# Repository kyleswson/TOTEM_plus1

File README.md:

<picture align="center">
  <source media="(prefers-color-scheme: dark)" srcset="/docs/images/TOTEM_logo_dark.svg">
  <source media="(prefers-color-scheme: light)" srcset="/docs/images/TOTEM_logo_bright.svg">
  
</picture>

<h1 align="center">T O T E M</h1>

TOTEM is a 38 key column-staggered choc split keyboard. It is meant to be used with a [Seeed Studio XIAO nRF52840 BLE](https://www.seeedstudio.com/Seeed-XIAO-BLE-nRF52840-p-5201.html) or [XIAO RP2040](https://www.seeedstudio.com/XIAO-RP2040-v1-0-p-5026.html).
It was created for the SEEED XIAO keyboard contest.\
[Here](https://www.hackster.io/geist/totem-a-tiny-splitkeyboard-with-splay-cb2e43) you can read about the process of making it.

## Companion Totem (TOTEM+1)
Totem+1 is a modified version of TOTEM by GEIGEIGEIST. It has additional one key on inner index column of each side (total 40 keys). This is because typing in Korean needs the "B" key on the right hand side. So I added additional B key on the right. And to make this keyboard symmetrical, I added it on the left side too. 

The inner thumb keys have been replaced to [EVQWGD001 roller encoders](https://a.aliexpress.com/_c3mfh3fF). Thought this will be handy for navigating cursor while typing. These are very expensive now(25$ for 1) but luckily I got it for 5$ each few years ago. \
I also found some alternatives that you can consider. But you may need to edit the PCB since the footprint will be different.\
https://github.com/kumamuk-git/CKW12 \
https://github.com/Taro-Hayashi/THQWGD001 \
https://github.com/EverydayErgo/MEH01 

For the batteries, I used this [305060 1100mAh battery](https://a.aliexpress.com/_c3kIPq6d) since I wanted long battery life. 

***

## LAYOUT

***

## PCB

[Here](/PCB/) you can find the KiCad files and Gerbers for the TOTEM.

***

## CASE

You can use the TOTEM without a case, but [here](/case/) you can find one I made for it.

***

## BUILD GUIDE

The build guide for the TOTEM can be found [here](/docs/buildguide.md).

***

## FIRMWARE

[QMK (VIAL) precompiled](/firmware/QMK/) or [QMK (VIAL) source](/firmware/QMK/VIAL_source/) for the TOTEM (wired using the XIAO RP2040)\
[ZMK precompiled](/firmware/ZMK/) or [ZMK source (outdated)](https://github.com/GEIGEIGEIST/zmk-config-totem) for the TOTEM (wireless using the XIAO BLE)

***

## BUY

You can buy TOTEM kits and finished builds on [keeb.supply](https://keeb.supply/products/geist-totem) (based in Germany)

***

## PHOTOS

This is the TOTEM in a black resin case

\
\

This is the TOTEM with a black resin tenting bottom plate

\
[Video by *Wolfgang's Channel* showing the tenting system in action](https://youtu.be/rvM2BthjEI4?si=mTJVdPeZstshnDyo)

***

## CREDITS

### INSPIRATION

I've added the additional pinky key to make the TOTEM compatible with the layout boards like the [Balbuzard](https://github.com/brow/balbuzard) by [Tom Brow](https://github.com/brow) and the [Osprette](https://github.com/smores56/osprette) by [Sam Mohr](https://github.com/smores56) use, where you put the keybinding of the top left and right keys on an outer pinky key.

### HELP FIXING THINGS

People who helped me create this board and fix stuff

#### PCB
- [Marco "Bob"](https://github.com/GroooveBob)

#### CASE
- [Freya](https://github.com/freya-irl)
- [Bubbleology](https://github.com/bubbleology)

#### FIRMWARE
- [Cem Aksoylar](https://github.com/caksoylar)
- [Grinnie](https://github.com/regicidalplutophage)
- [Alaa Saad Mansour](https://github.com/AlaaSaadAbdo)
- [pekudzu](https://github.com/pekudzu)

If you build a TOTEM I would be pretty happy to see some pictures. And if you want to leave me a tip you can do this [here](https://ko-fi.com/geigeigeist) (but please don't feel pressured)

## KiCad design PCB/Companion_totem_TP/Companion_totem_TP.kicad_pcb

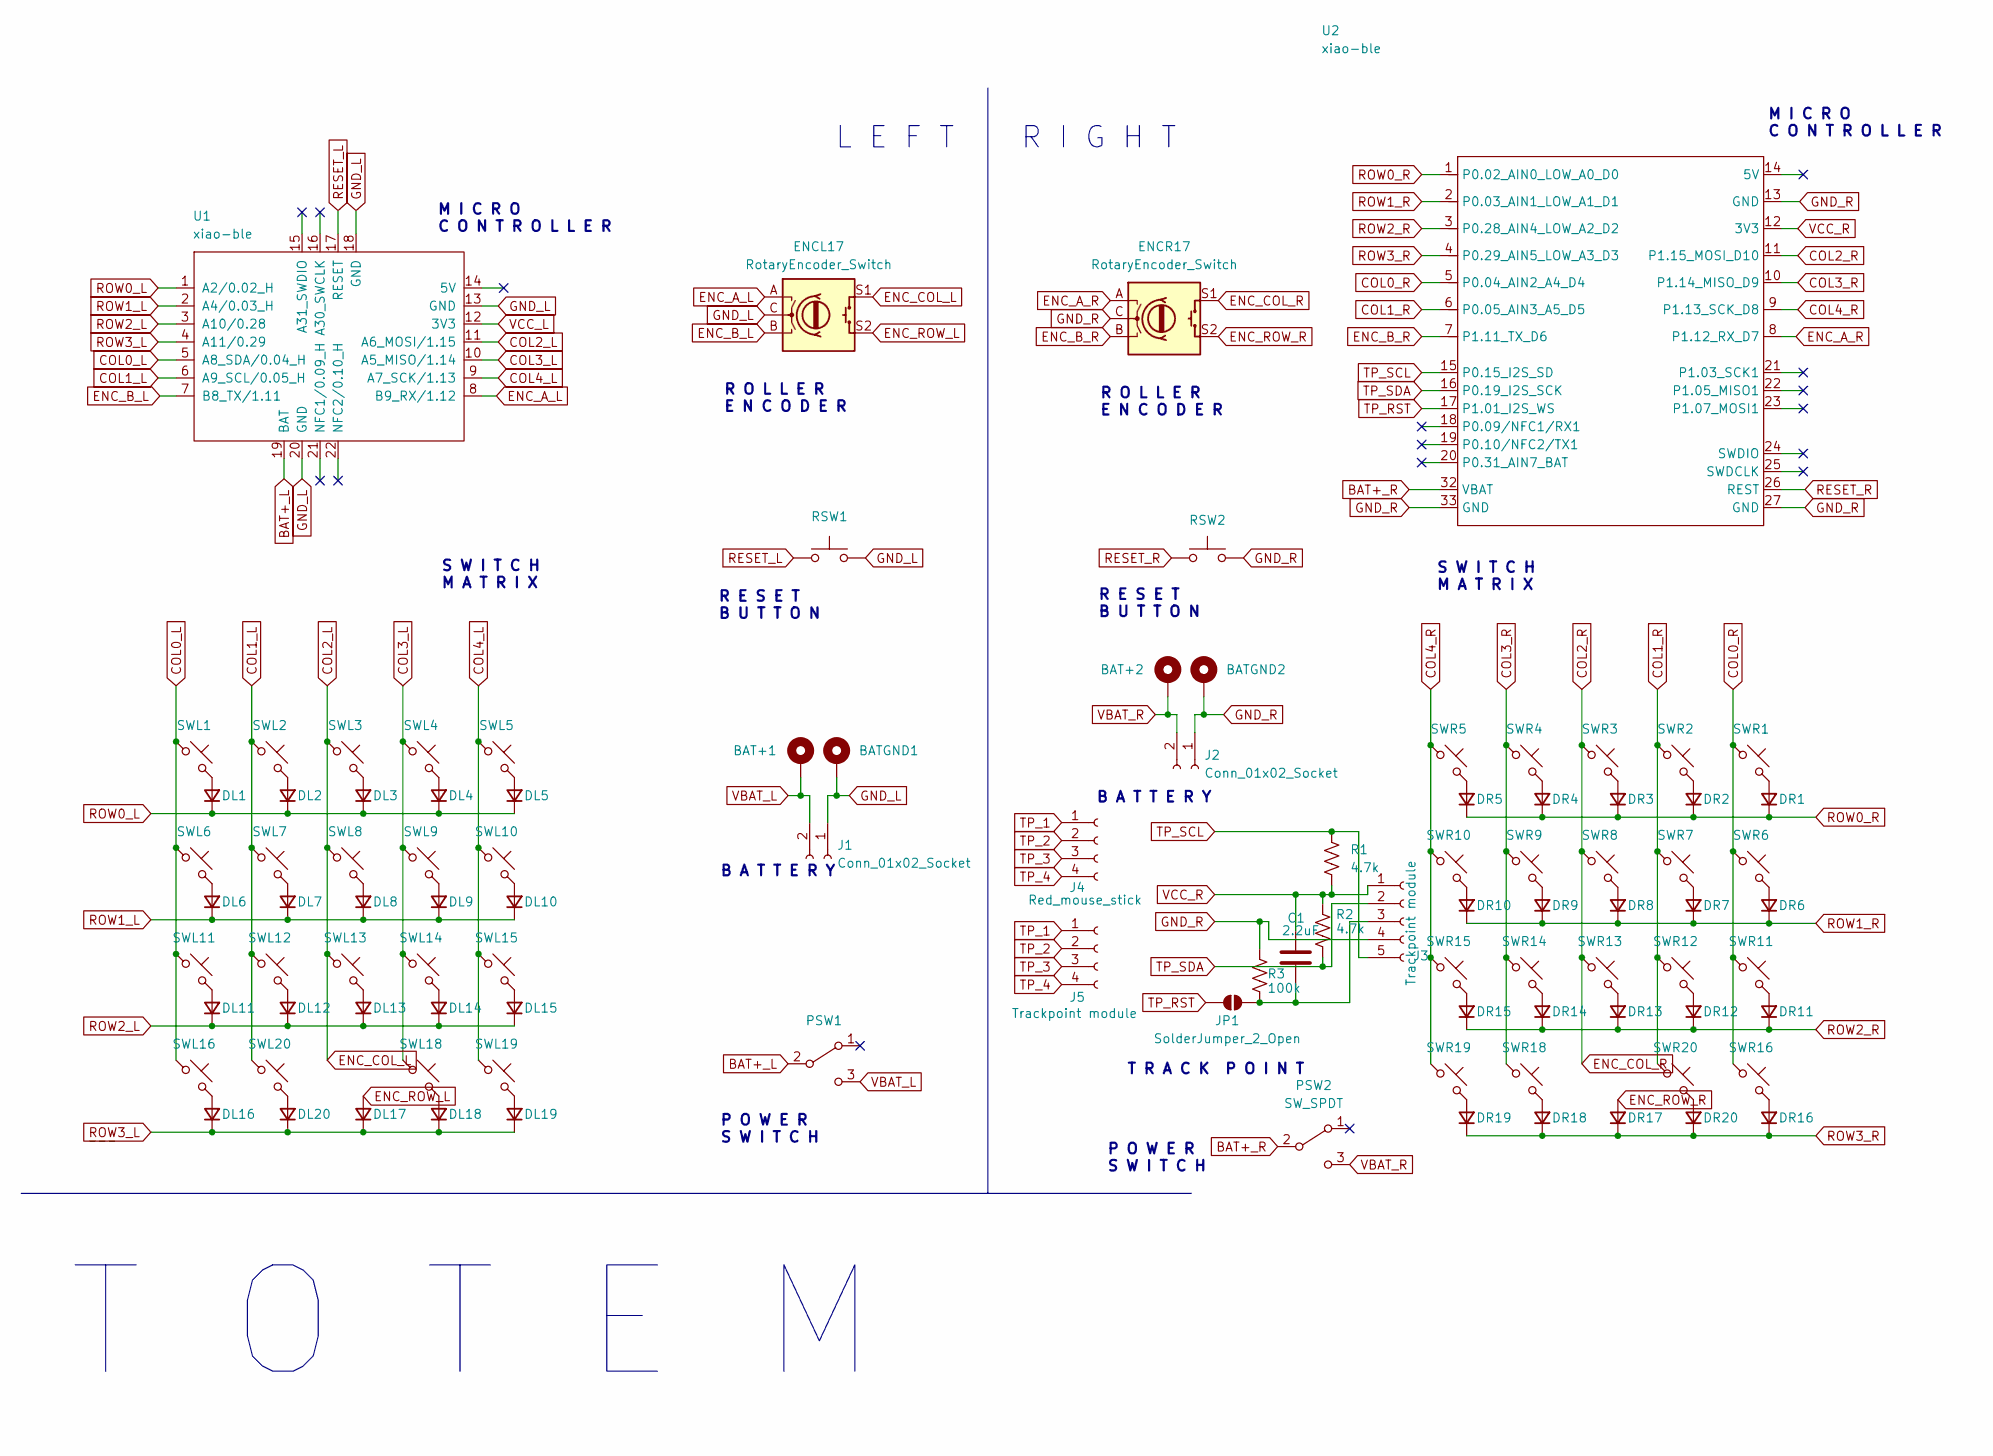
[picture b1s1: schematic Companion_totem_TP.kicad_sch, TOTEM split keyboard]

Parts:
BAT+1, BAT+2: +; BatteryPad
BATGND1, BATGND2: -; BatteryPad
C1: 2.2uF; C_0603_1608Metric_Pad1.08x0.95mm_HandSolder
DL1, DL2, DL3, DL4, DL5, DL6, DL7, DL8, DL9, DL10, DL11, DL12, DL13, DL14, DL15, DL16, DL17, DL18, DL19, DL20: D_Small; Diode_SOD123
DR1, DR2, DR3, DR4, DR5, DR6, DR7, DR8, DR9, DR10, DR11, DR12, DR13, DR14, DR15, DR16, DR17, DR18, DR19, DR20: D_Small; Diode_SOD123
ENCL17: RotaryEncoder_Switch; RollerEncoder+SW_horizontal
ENCR17: RotaryEncoder_Switch; RollerEncoder_SW_Vertical
J1, J2: Conn_01x02_Socket
J3: Trackpoint module; PinSocket_1x05_P2.54mm_Vertical
J4: Red_mouse_stick; T460S_TP
J5: Trackpoint module; TP_input
JP1: SolderJumper_2_Open; Jumper
PSW1, PSW2: SW_SPDT; MSK12C02
R1, R2: 4.7k; R_0603_1608Metric_Pad0.98x0.95mm_HandSolder
R3: 100k; R_0603_1608Metric_Pad0.98x0.95mm_HandSolder
RSW1, RSW2: SW_Push; SKHLLCA010
SWL1, SWL2, SWL3, SWL4, SWL5, SWL6, SWL7, SWL8, SWL9, SWL10, SWL11, SWL12, SWL13, SWL14, SWL15, SWL16, SWL18, SWL19, SWL20: SW_Push_45deg; Kailh_socket_PG1350
SWR1, SWR2, SWR3, SWR4, SWR5, SWR6, SWR7, SWR8, SWR9, SWR10, SWR11, SWR12, SWR13, SWR14, SWR15, SWR16, SWR18, SWR19, SWR20: SW_Push_45deg; Kailh_socket_PG1350
U1: xiao-ble; xiao-ble-smd-cutout
U2: xiao-ble; XIAO-nRF52840-Plus-SMD

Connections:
BAT+_L: PSW1.2 (B), U1.19 (BAT)
BAT+_R: PSW2.2 (B), U2.32 (VBAT)
COL0_L: SWL1.1, SWL6.1, SWL11.1, SWL16.1, U1.5 (A8_SDA/0.04_H)
COL0_R: SWR1.1, SWR6.1, SWR11.1, SWR16.1, U2.5 (P0.04_AIN2_A4_D4)
COL1_L: SWL2.1, SWL7.1, SWL12.1, SWL20.1, U1.6 (A9_SCL/0.05_H)
COL1_R: SWR2.1, SWR7.1, SWR12.1, SWR20.1, U2.6 (P0.05_AIN3_A5_D5)
COL2_L: ENCL17.S1, SWL3.1, SWL8.1, SWL13.1, U1.11 (A6_MOSI/1.15)
COL2_R: ENCR17.1, ENCR17.2, ENCR17.S1, SWR3.1, SWR8.1, SWR13.1, U2.11 (P1.15_MOSI_D10)
COL3_L: SWL4.1, SWL9.1, SWL14.1, SWL18.1, U1.10 (A5_MISO/1.14)
COL3_R: SWR4.1, SWR9.1, SWR14.1, SWR18.1, U2.10 (P1.14_MISO_D9)
COL4_L: SWL5.1, SWL10.1, SWL15.1, SWL19.1, U1.9 (A7_SCK/1.13)
COL4_R: SWR5.1, SWR10.1, SWR15.1, SWR19.1, U2.9 (P1.13_SCK_D8)
ENC_A_L: ENCL17.A, U1.8 (B9_RX/1.12)
ENC_A_R: ENCR17.A, U2.8 (P1.12_RX_D7)
ENC_B_L: ENCL17.B, U1.7 (B8_TX/1.11)
ENC_B_R: ENCR17.B, U2.7 (P1.11_TX_D6)
ENC_ROW_L: DL17.2 (A), ENCL17.S2
ENC_ROW_R: DR17.2 (A), ENCR17.1, ENCR17.2, ENCR17.S2
GND_L: BATGND1.1, ENCL17.C, J1.1, RSW1.2, U1.13 (GND), U1.18 (GND), U1.20 (GND)
GND_R: BATGND2.1, ENCR17.C, J2.1, J3.4, R3.1, RSW2.2, U2.13 (GND), U2.27 (GND), U2.33 (GND); also elsewhere on the board
unnamed: DL1.2 (A), SWL1.2
unnamed: DL2.2 (A), SWL2.2
unnamed: DL3.2 (A), SWL3.2
unnamed: DL4.2 (A), SWL4.2
unnamed: DL5.2 (A), SWL5.2
unnamed: DL6.2 (A), SWL6.2
unnamed: DL7.2 (A), SWL7.2
unnamed: DL8.2 (A), SWL8.2
unnamed: DL9.2 (A), SWL9.2
unnamed: DL10.2 (A), SWL10.2
unnamed: DL11.2 (A), SWL11.2
unnamed: DL12.2 (A), SWL12.2
unnamed: DL13.2 (A), SWL13.2
unnamed: DL14.2 (A), SWL14.2
unnamed: DL15.2 (A), SWL15.2
unnamed: DL16.2 (A), SWL16.2
unnamed: DL18.2 (A), SWL18.2
unnamed: DL19.2 (A), SWL19.2
unnamed: DL20.2 (A), SWL20.2
unnamed: DR1.2 (A), SWR1.2
unnamed: DR2.2 (A), SWR2.2
unnamed: DR3.2 (A), SWR3.2
unnamed: DR4.2 (A), SWR4.2
unnamed: DR5.2 (A), SWR5.2
unnamed: DR6.2 (A), SWR6.2
unnamed: DR7.2 (A), SWR7.2
unnamed: DR8.2 (A), SWR8.2
unnamed: DR9.2 (A), SWR9.2
unnamed: DR10.2 (A), SWR10.2
unnamed: DR11.2 (A), SWR11.2
unnamed: DR12.2 (A), SWR12.2
unnamed: DR13.2 (A), SWR13.2
unnamed: DR14.2 (A), SWR14.2
unnamed: DR15.2 (A), SWR15.2
unnamed: DR16.2 (A), SWR16.2
unnamed: DR18.2 (A), SWR18.2
unnamed: DR19.2 (A), SWR19.2
unnamed: DR20.2 (A), SWR20.2
unnamed 58: C1.2, J3.3, JP1.2 (B), R3.2; also elsewhere on the board
RESET_L: RSW1.1, U1.17 (RESET)
RESET_R: RSW2.1, U2.26 (REST)
ROW0_L: DL1.1 (K), DL2.1 (K), DL3.1 (K), DL4.1 (K), DL5.1 (K), U1.1 (A2/0.02_H)
ROW0_R: DR1.1 (K), DR2.1 (K), DR3.1 (K), DR4.1 (K), DR5.1 (K), U2.1 (P0.02_AIN0_LOW_A0_D0)
ROW1_L: DL6.1 (K), DL7.1 (K), DL8.1 (K), DL9.1 (K), DL10.1 (K), U1.2 (A4/0.03_H)
ROW1_R: DR6.1 (K), DR7.1 (K), DR8.1 (K), DR9.1 (K), DR10.1 (K), U2.2 (P0.03_AIN1_LOW_A1_D1)
ROW2_L: DL11.1 (K), DL12.1 (K), DL13.1 (K), DL14.1 (K), DL15.1 (K), U1.3 (A10/0.28)
ROW2_R: DR11.1 (K), DR12.1 (K), DR13.1 (K), DR14.1 (K), DR15.1 (K), U2.3 (P0.28_AIN4_LOW_A2_D2)
ROW3_L: DL16.1 (K), DL17.1 (K), DL18.1 (K), DL19.1 (K), DL20.1 (K), U1.4 (A11/0.29)
ROW3_R: DR16.1 (K), DR17.1 (K), DR18.1 (K), DR19.1 (K), DR20.1 (K), U2.4 (P0.29_AIN5_LOW_A3_D3)
TP_1: J4.1, J5.1; also elsewhere on the board
TP_2: J4.2, J5.2; also elsewhere on the board
TP_3: J4.3, J5.3; also elsewhere on the board
TP_4: J4.4, J5.4; also elsewhere on the board
TP_RST: JP1.1 (A), U2.17 (P1.01_I2S_WS)
TP_SCL: J3.5, R1.1, U2.15 (P0.15_I2S_SD); also elsewhere on the board
TP_SDA: J3.2, R2.2, U2.16 (P0.19_I2S_SCK); also elsewhere on the board
VBAT_L: BAT+1.1, J1.2, PSW1.3 (C)
VBAT_R: BAT+2.1, J2.2, PSW2.3 (C)
VCC_L: U1.12 (3V3)
VCC_R: C1.1, J3.1, R1.2, R2.1, U2.12 (3V3); also elsewhere on the board

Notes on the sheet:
M I C R O C O N T R O L L E R
R E S E T B U T T O N
S W I T C H M A T R I X
P O W E R S W I T C H
T O T E M
B A T T E R Y
R O L L E R E N C O D E R
T R A C K P O I N T
R I G H T
L E F T

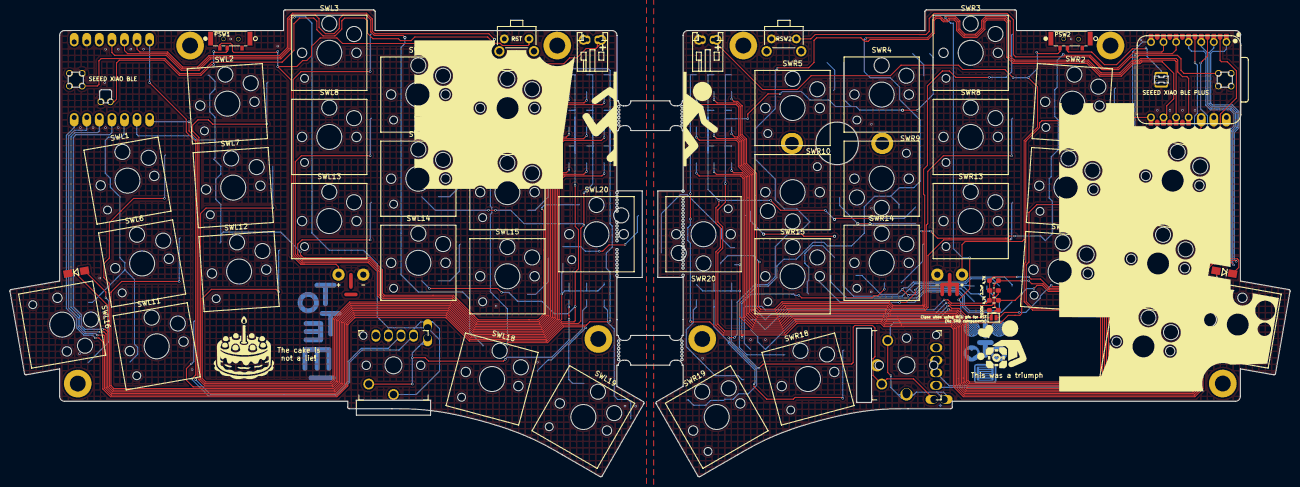
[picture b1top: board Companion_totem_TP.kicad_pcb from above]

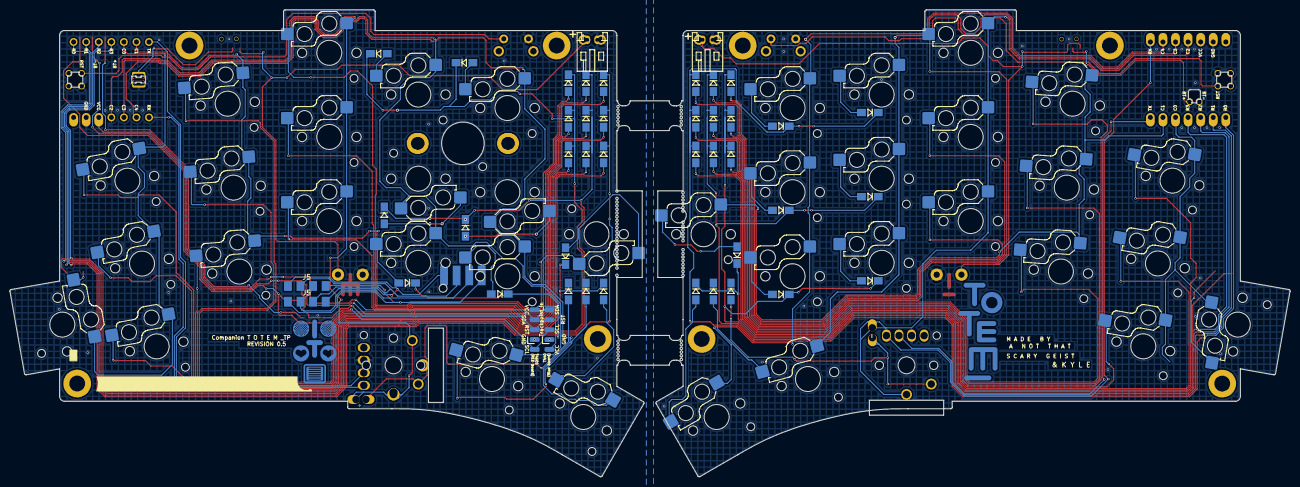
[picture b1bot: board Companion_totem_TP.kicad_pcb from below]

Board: 2 copper layers, 258.7 x 94.4 mm, 102 parts (40 on the bottom side), 79 nets.

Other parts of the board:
J5#2: Trackpoint module; TP_input
Trackpoint_in: Trackpoint module; PinSocket_1x05_P2.54mm_Vertical

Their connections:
GND_R: Trackpoint_in.4; also elsewhere on the board
unnamed 58: Trackpoint_in.2; also elsewhere on the board
TP_1: J5#2.1 (Pin_4); also elsewhere on the board
TP_2: J5#2.2 (Pin_3); also elsewhere on the board
TP_3: J5#2.3 (Pin_2); also elsewhere on the board
TP_4: J5#2.4 (Pin_1); also elsewhere on the board
TP_SCL: Trackpoint_in.3; also elsewhere on the board
TP_SDA: Trackpoint_in.1; also elsewhere on the board
VCC_R: Trackpoint_in.5; also elsewhere on the board

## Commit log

2025-06-03 new totemkyle
2025-06-04 add encoder & switch
2025-06-05 Add 1 key and roller encoder
2025-06-08 Added case
2025-06-09 Battery
2025-06-18 add jst connector for battery
2026-01-13 Adding Track Point
2026-01-22 Added TP, Split L&R
